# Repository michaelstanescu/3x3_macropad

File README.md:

# 3x3 Macropad (with Rotary Encoder)

A custom-designed, fully programmable mechanical macropad built to streamline desktop workflows and demonstrate full-cycle hardware development and embedded firmware integration. 

## System Features

*   **PCB Layout:** A compact 3x3 grid (9 keys) designed for macros, shortcuts, or a dedicated numpad.
*   **Rotary Encoder:** A clickable dial mapped for master volume control and audio muting.
*   **Microcontroller:** Arduino Pro Micro (ATmega32U4).
*   **Firmware:** QMK Firmware integration, allowing complete customization of every key switch and encoder action.
*   **Other Components:** Custom 3D-printed keycaps and rotary encoder knob.

## Hardware Design (KiCad)

The hardware architecture and PCB layout were developed using KiCad 10.0:

*   **Schematics:** A 3x3 switch matrix configured with diodes to prevent key ghosting, alongside integrated pin mappings for the rotary encoder and microcontroller.
*   **PCB Layout:** A compact board layout with optimized trace routing.

## QMK Firmware

The `/firmware` directory contains the configuration files (`keymap.c`, `keyboard.json`, and `rules.mk`) required to compile and flash the system for custom keybindings.

## Repository Structure

*   `/` (Root): The primary KiCad design files (`macropadpcb.kicad_pro`, `macropadpcb.kicad_sch`, `macropadpcb.kicad_pcb`).
*   `/firmware`: The QMK configuration source files.
*   `/docs`: System architecture documentation, including a PDF of the PCB layout, schematics, 3D renders, and physical images of the final build.

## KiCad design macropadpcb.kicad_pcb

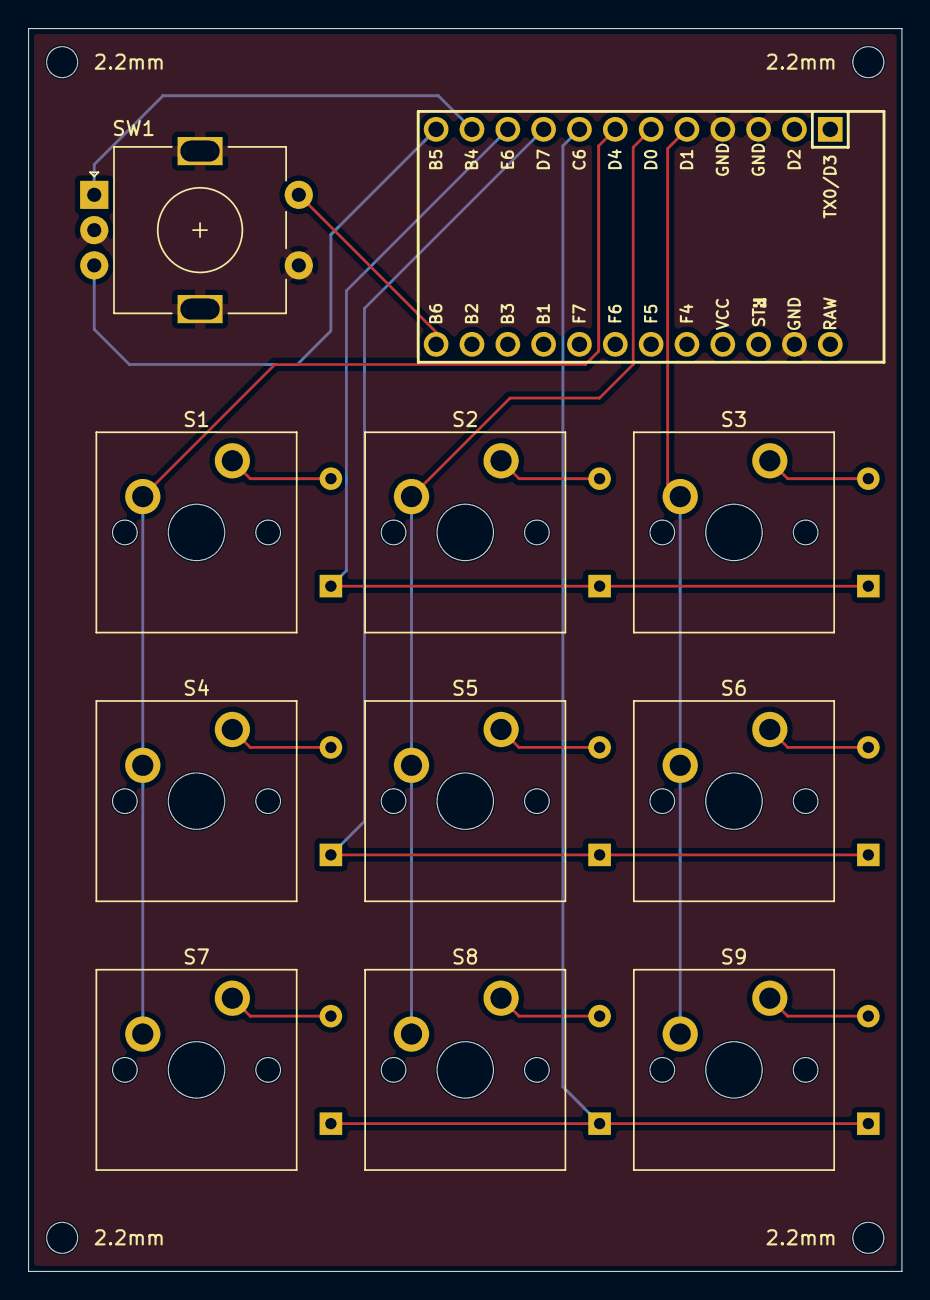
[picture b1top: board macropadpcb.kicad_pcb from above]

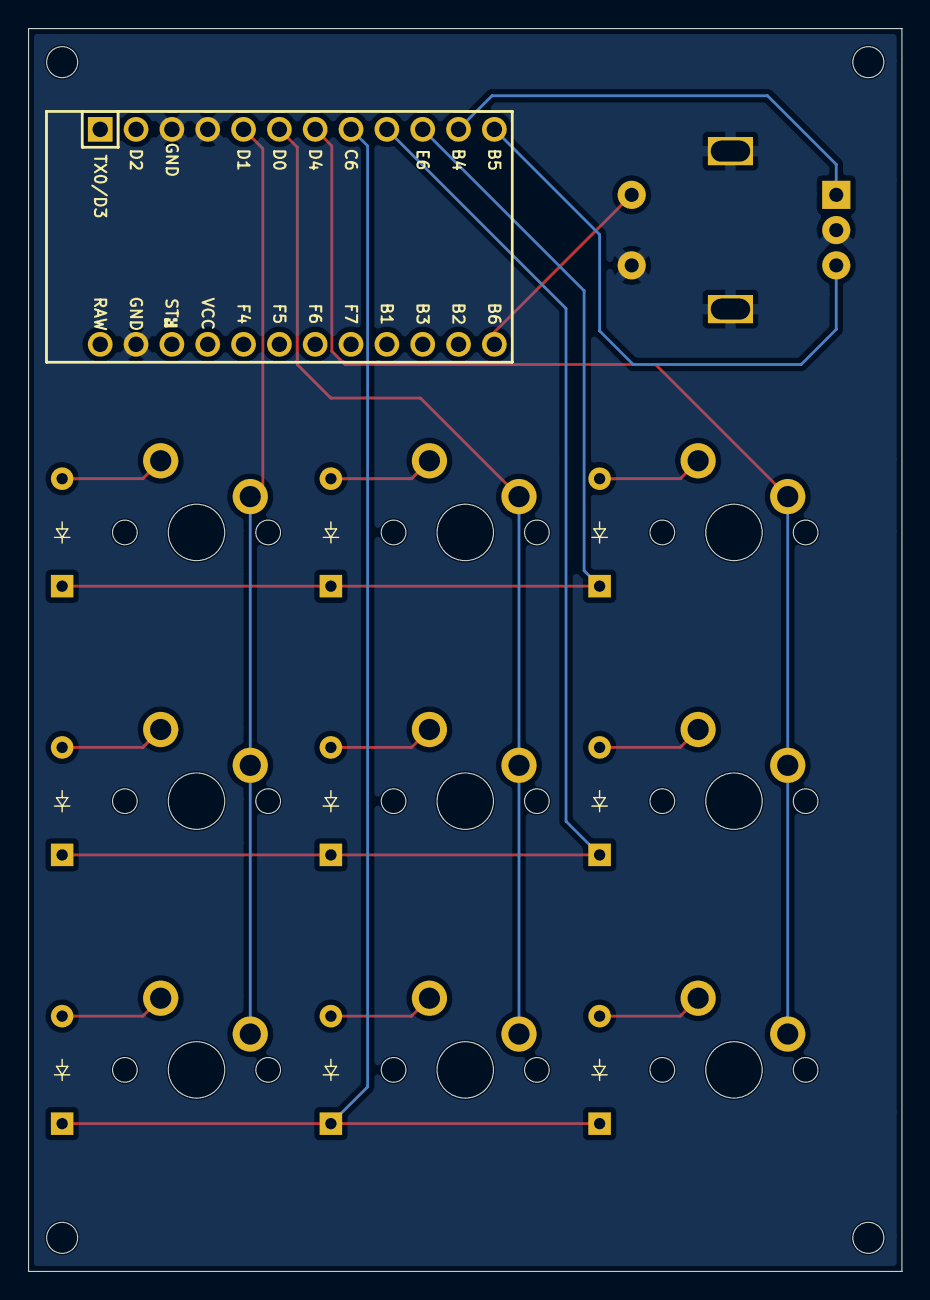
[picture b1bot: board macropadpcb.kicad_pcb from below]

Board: 2 copper layers, 61.9 x 88.1 mm, 24 parts (9 on the bottom side), 19 nets.

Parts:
2.2mm, 2.2mm#2, 2.2mm#3, 2.2mm#4: MountingHole_2.2mm_M2
D1, D2, D3, D4, D5, D6, D7, D8, D9: Diode_DO-35
S1, S2, S3, S4, S5, S6, S7, S8, S9: MX_PCB_1.00u
SW1: RotaryEncoder_Switch; RotaryEncoder_Alps_EC11E-Switch_Vertical_H20mm
U1: Arduino_Pro_Micro

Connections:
Column 0: S1.1, S4.1, S7.1, U1.7 (4/PD4)
Column 1: S2.1, S5.1, S8.1, U1.6 (3/PD0)
Column 2: S3.1, S6.1, S9.1, U1.5 (2/PD1)
ENC_A: SW1.A, U1.11 (8/PB4)
ENC_B: SW1.B, U1.12 (9/PB5)
ENC_SW: SW1.S2, U1.13 (10/PB6)
GND: SW1.C, SW1.MP, SW1.S1, U1.3 (GND), U1.4 (GND), U1.23 (GND)
unnamed: D1.2 (A), S1.2
unnamed: D2.2 (A), S2.2
unnamed: D3.2 (A), S3.2
unnamed: D4.2 (A), S4.2
unnamed: D5.2 (A), S5.2
unnamed: D6.2 (A), S6.2
unnamed: D7.2 (A), S7.2
unnamed: D8.2 (A), S8.2
unnamed: D9.2 (A), S9.2
Row 0: D1.1 (K), D2.1 (K), D3.1 (K), U1.10 (7/PE6)
Row 1: D4.1 (K), D5.1 (K), D6.1 (K), U1.9 (6/PD7)
Row 2: D7.1 (K), D8.1 (K), D9.1 (K), U1.8 (5/PC6)
